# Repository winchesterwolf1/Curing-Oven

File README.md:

Codebase to run a simple UI for a UV curing station created from a UV bulb, Arduino Nano, SPI OLED screen, and a digital encoder

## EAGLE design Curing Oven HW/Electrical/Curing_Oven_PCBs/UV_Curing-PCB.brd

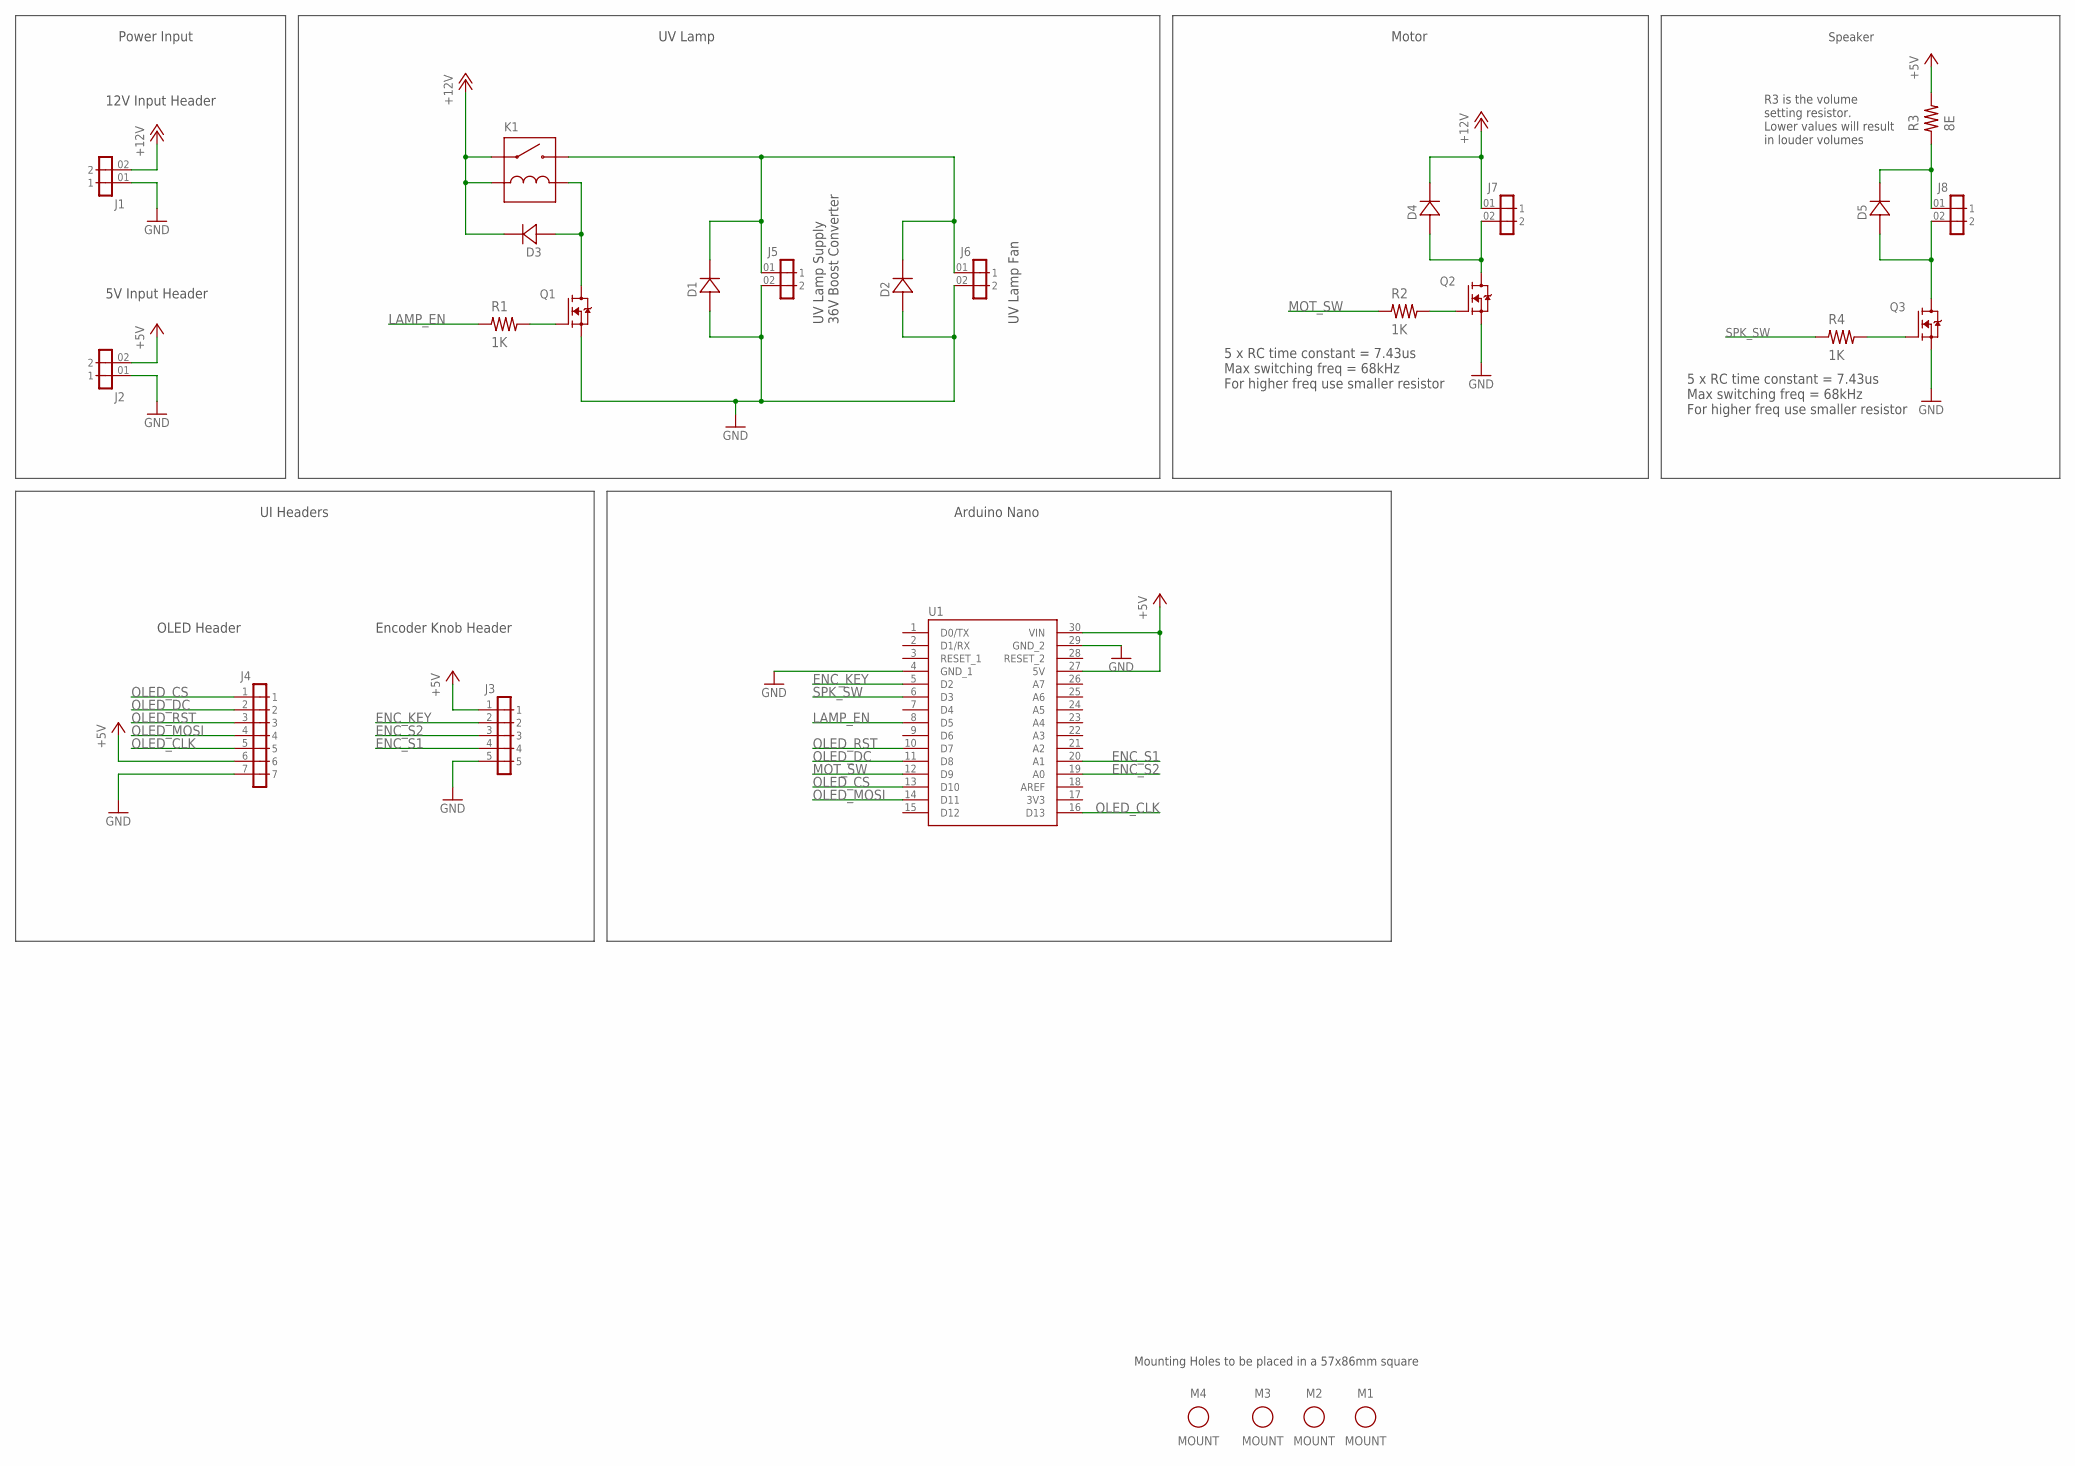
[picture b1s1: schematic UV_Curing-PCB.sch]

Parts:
D1, D2, D3, D4, D5: 400V; DIOAD520W79L463D238
J1, J2, J5, J6, J7, J8: PINHEADER-2POS-2.54MM; 254-1X02-PIN
J3: PINHEADER-5POS-2.54MM; 254-1X05-PIN
J4: PINHEADER-7POS-2.54MM; 254-1X07-PIN
K1: 25V; JY25HK505
M1, M2, M3, M4: MOUNTING_HOLE; M4_NP_MOUNTING_HOLE
Q1, Q2, Q3: 55V; TO254P1016X419X2286-3
R1, R2, R4: 1K; RES-THRU
R3: 8E; RES-THRU
U1: A000005; MODULE_A000005

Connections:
3V3: U1.17 (3V3)
+5V: J2.02 (2), J3.1, J4.6, R3.2, U1.27 (5V), U1.30 (VIN)
+12V: D3.C, D4.C, J1.02 (2), J7.01 (1), K1.8 (COIL_1), K1.16 (COM)
ENC_KEY: J3.2, U1.5 (D2)
ENC_S1: J3.4, U1.20 (A1)
ENC_S2: J3.3, U1.19 (A0)
GND: D1.A, D2.A, J1.01 (1), J2.01 (1), J3.5, J4.7, J5.02 (2), J6.02 (2), Q1.3 (S), Q2.3 (S), Q3.3 (S), U1.4 (GND_1), U1.29 (GND_2)
LAMP_EN: R1.1, U1.8 (D5)
MOT_SW: R2.1, U1.12 (D9)
unnamed: Q1.1 (G), R1.2
unnamed: D1.C, D2.C, J5.01 (1), J6.01 (1), K1.13 (NO)
unnamed: D3.A, K1.9 (COIL_2), Q1.2 (D)
unnamed: Q2.1 (G), R2.2
unnamed: D4.A, J7.02 (2), Q2.2 (D)
unnamed: D5.C, J8.01 (1), R3.1
unnamed: D5.A, J8.02 (2), Q3.2 (D)
unnamed: Q3.1 (G), R4.2
OLED_CLK: J4.5, U1.16 (D13)
OLED_CS: J4.1, U1.13 (D10)
OLED_DC: J4.2, U1.11 (D8)
OLED_MOSI: J4.4, U1.14 (D11)
OLED_RST: J4.3, U1.10 (D7)
SPK_SW: R4.1, U1.6 (D3)

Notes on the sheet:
Arduino Nano
Power Input
12V Input Header
5V Input Header
UI Headers
OLED Header
Encoder Knob Header
UV Lamp
UV Lamp Supply 36V Boost Converter
UV Lamp Fan
Motor
5 x RC time constant = 7.43us Max switching freq = 68kHz For higher freq use smaller resistor
Speaker
R3 is the volume setting resistor. Lower values will result in louder volumes
Mounting Holes to be placed in a 57x86mm square

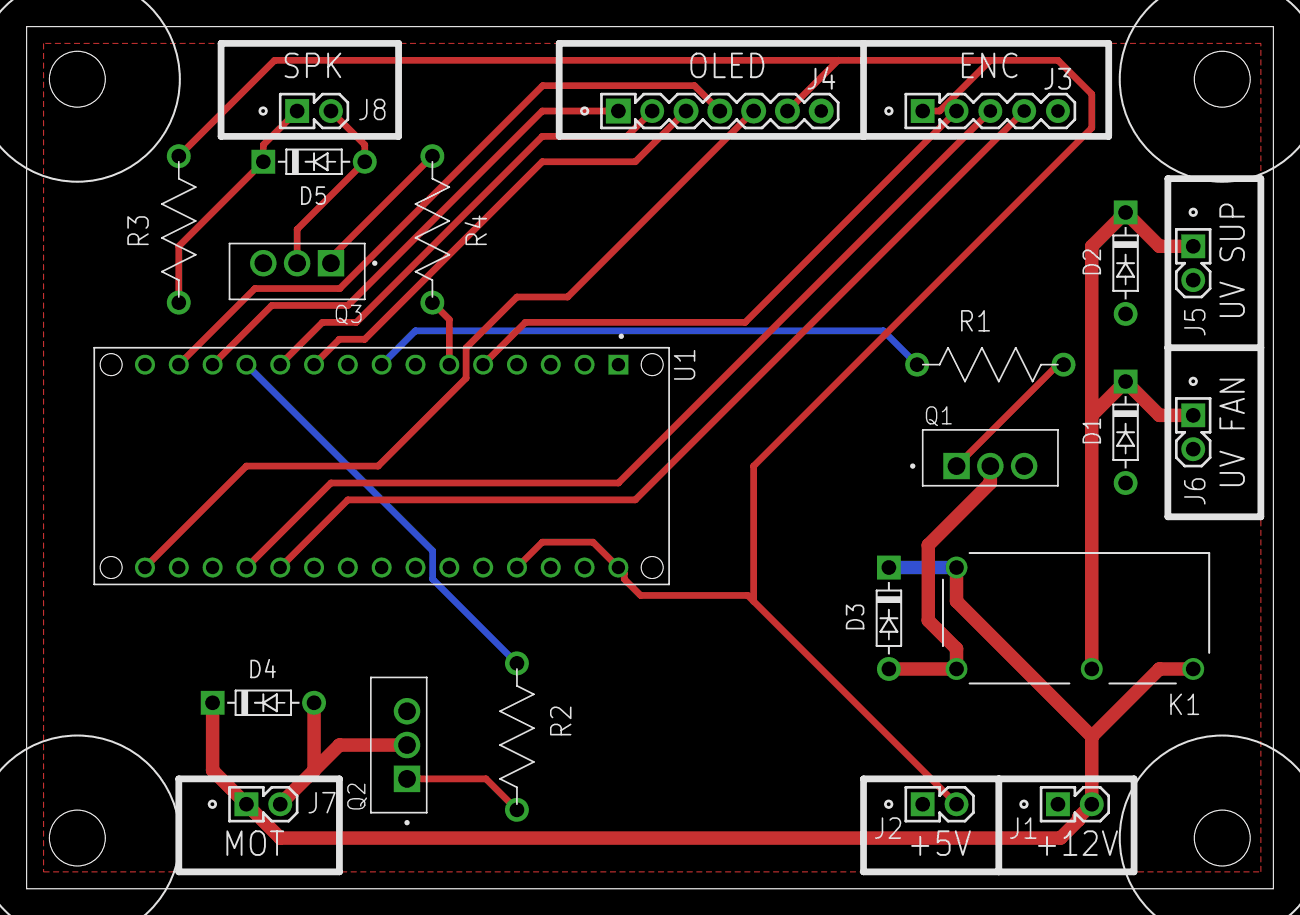
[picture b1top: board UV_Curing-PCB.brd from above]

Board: 2 copper layers, 93.7 x 64.8 mm, 26 parts (0 on the bottom side), 22 nets.

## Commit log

2025-09-29 Initial Commits
2025-09-29 Added comments
2025-09-29 Added Speaker beeps and motor stuff to UI
2025-10-04 Tidied up main and created a pseudo RTOS
2025-10-05 Updated PseudoRtos structure to be perfectly object oriented
2025-10-05 Finished tidying up and documenting entire codebase
2025-10-28 Updated PCB for fab manufacturing
2025-10-28 Removed autosaves,
    Added Gerber outputs
2025-11-10 fixed error in encoder knob placement
2026-05-03 Added EEPROM HAL library folders
